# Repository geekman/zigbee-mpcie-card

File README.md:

CC2538 Zigbee mPCIe Adapter
============================

For use with [zigbee2mqtt](https://www.zigbee2mqtt.io/).

This card is basically a USB-to-serial adapter for the CC2538 + CC2592 PA Zigbee module.
It is intended for use in host devices that accept mPCIe cards, instead of having a Zigbee dongle sticking out of the USB port.
The antenna connection is also brought out to an external SMA connector via a U.FL pigtail.

As with most of my boards, this was designed to be flexible. The TX and RX pins from the module are clearly marked, so that the card can be repurposed as a generic serial device mPCIe card.
There are also various test points for I²C, as well as control for the WLAN/WWAN LEDs that are on the host machine.

This project is authored in [KiCad EDA](https://www.kicad.org/).
You can find schematics and the BOM under the [Releases](https://github.com/geekman/zigbee-mpcie-card/releases) section.

Assembly Instructions
======================

Please be aware that there are a few variations of this CC2538 module with different pinouts and dimensions.
The one I bought, and used in this mPCIe card, is available on [AliExpress here](https://www.aliexpress.com/item/4000748032872.html).
Also note that the presence of an on-board antenna; the module needs to be physically configured to use the U.FL connector instead of the on-board antenna.
You will need to indicate this to the seller, or you can modify it yourself by moving a capacitor (or resistor, not sure what that part is).

The card has support for native USB connectivity to the CC2538, but it is not used. 
As such, the component on the back side should not be populated, as well as R2 on the front side. The BOM file has these parts marked as DNP.

Additionally, Q2 was added for an ESP8266-style auto reset, but since the `cc2538-bsl` does not support this style of bootloader invocation, the pins of Q2 need to be manually bridged. The new revision of PCB has these connections marked out on the silkscreen.

Testing
--------

When inserted, the card should be detected as a CP2102N USB device on the host.

You need the [cc2538-bsl](https://github.com/JelmerT/cc2538-bsl) Python tool, 
which only depends on `pyserial`.
Note that the tool will try to reconnect to the port with an increased baud rate for faster transfer speeds, but this was causing problems for me. Use `-b` to set a fixed baud rate, and choose a lower value for stability.

You can test that the mPCIe card is properly detected by reading from the CC2538 with `-r`:

```
$ python3 cc2538-bsl.py -b 500000 -r test.bin
Opening port /dev/ttyUSB0, baud 500000
Connecting to target...
CC2538 PG2.0: 512KB Flash, 32KB SRAM, CCFG at 0x0027FFD4
Primary IEEE Address: 00:12:4B:00:19:4A:F1:CE
Reading 524288 bytes starting at address 0x200000
 0x200xxx: 0xffffffff
```

If you do specify the `-V` verbose flag, you see that chip ID for the CC2538 has been correctly detected:

```
$ python3 cc2538-bsl.py -V -r test.bin
Opening port /dev/ttyUSB0, baud 500000
Connecting to target...
*** sending synch sequence
Got 0 additional bytes before ACK/NACK
*** GetChipId command (0x28)
Got 0 additional bytes before ACK/NACK
*** received 6 bytes
*** GetStatus command (0x23)
Got 0 additional bytes before ACK/NACK
*** received 3 bytes
Command Successful
    Version 0x0000B964
    Target id 0xb964, CC2538
  .
  .
  .
```

Firmware Flashing
==================

You can download a zigbee2mqtt-compatible firmware here:

- <https://github.com/jethome-ru/zigbee-firmware/tree/master/ti/coordinator/cc2538_cc2592>

Here are some other firmware for reference:

- <https://github.com/egony/MODKAM-STICK-V3/tree/master/firmware/cc2538/Riverieline_2020-02>
- <https://github.com/Koenkk/Z-Stack-firmware/tree/master/coordinator>

You can choose either one; I went with the JetHome one.

Use the `cc2538-bsl.py` tool with `-w -v` to write and verify the firmware file.
Both the `.bin` and `.hex` contain the same firmware, just in a different format.

```
$ python3 cc2538-bsl.py -b 115200 -w -v JH_2538_2592_ZNP_UART_20201010.bin
Opening port /dev/ttyUSB0, baud 115200
Reading data from JH_2538_2592_ZNP_UART_20201010.bin
Cannot auto-detect firmware filetype: Assuming .bin
Connecting to target...
CC2538 PG2.0: 512KB Flash, 32KB SRAM, CCFG at 0x0027FFD4
Primary IEEE Address: 00:12:4B:00:19:4A:F1:CE
Writing 524256 bytes starting at address 0x00200000
Write 232 bytes at 0x0027FEF88
    Write done
Verifying by comparing CRC32 calculations.
    Verified (match: 0x6273805e)
```

You should now see the power LED on the mPCIe card light up.

Bootloader "Backdoor"
----------------------

Note that while the serial bootloader is a convenient way to program the CC2538, it may also be disabled by the firmware developer for security reasons.

The firmware images provided above all have this "bootloader backdoor" enabled, so that newer firmware can be flashed via the serial port.
This is done by setting some bits in the Customer Configuration Area (CCA) to enable the backdoor, and allowing for activation via pin `PA7`.
For more information, see the SWRA466 document here: <https://www.ti.com/lit/pdf/swra466>

You can verify this by opening the firmware HEX file and seeing the value `0xF7` set at `0x0027.FFD7`. (Actually the write begins at `0x27FFD4` to write a 32-bit value `FF FF FF F7`)

If you do not flash these bytes into the CCA, the serial bootloader can no longer be accessed and you will need JTAG to program the device. The connector has been brought out to the back side of the card, in case this is needed.

License
========
  
**cc2538-mpcie-card is licensed under the TAPR Open Hardware License (https://www.tapr.org/OHL).**

Copyright (C) 2021 Darell Tan

The TAPR Open Hardware License ("OHL") agreement provides a legal
framework for Open Hardware projects.
The OHL addresses unique issues involved in the creation of tangible,
physical things, but does not cover software, firmware, or code loaded
into programmable devices.

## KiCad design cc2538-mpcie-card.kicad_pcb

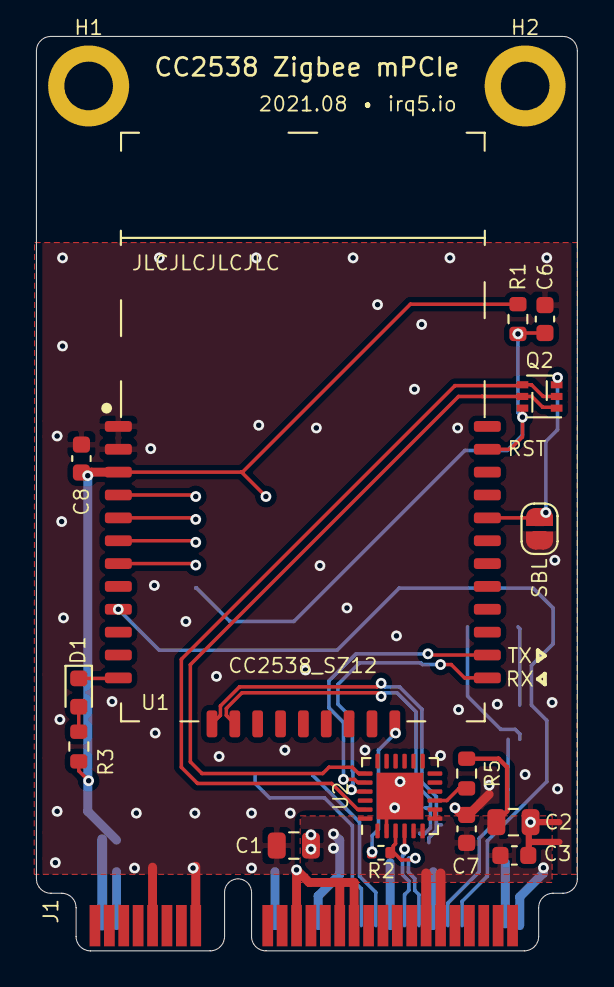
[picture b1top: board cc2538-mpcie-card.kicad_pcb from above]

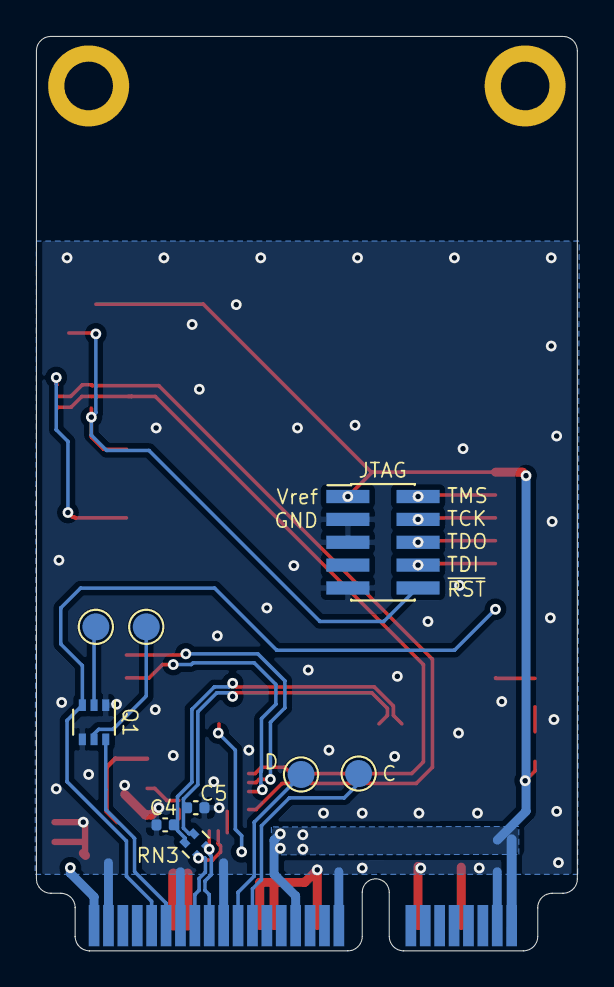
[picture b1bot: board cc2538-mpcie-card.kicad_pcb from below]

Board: 2 copper layers, 30.1 x 50.8 mm, 27 parts (9 on the bottom side), 26 nets.

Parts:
C1, C2: 47uF; C_0805_2012Metric
C3, C7: 0.1uF; C_0603_1608Metric
C4, C5: 47pF; C_0402_1005Metric
C6: 1nF; C_0603_1608Metric
C8: 10uF; C_0603_1608Metric
D1: LED_Small; LED_0603_1608Metric
H1, H2: MountingHole_Pad; MountingHole_2.7mm_M2.5_ISO7380_Pad
J1: Bus_PCI_Express_Mini; mPCIe_Card_Edge
J2: Conn_ARM_JTAG_SWD_10; PinHeader_2x05_P1.27mm_Vertical_SMD
JP1: SolderJumper_2_Open; SolderJumper-2_P1.3mm_Open_RoundedPad1.0x1.5mm
Q1, Q2: MUN5214DW1; SOT-363_SC-70-6
R1, R3, R5: 4K7; R_0603_1608Metric
R2: 1K5; R_0402_1005Metric
RN3: 33R; R_Array_Convex_2x0402
TP1: SDA; TestPoint_Pad_D1.5mm
TP2: SCL; TestPoint_Pad_D1.5mm
TP3: LED_WLAN; TestPoint_Pad_D1.5mm
TP4: LED_WWAN; TestPoint_Pad_D1.5mm
U1: CC2538_SZ12; CC2538_SZ12_Module
U2: CP2102N-A01-GQFN24; QFN-24-1EP_4x4mm_P0.5mm_EP2.6x2.6mm

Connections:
+3V3: C1.1, C2.1, C3.1, C7.2, C8.2, J1.2, J1.24, J1.39, J1.41, J1.52, J2.1, R1.2, R3.2, R5.1, U1.3, U2.5, U2.6, U2.7, U2.8
/CC_RST: C6.2, J2.10, Q2.6, R1.1, U1.32
/CC_RX: U1.22, U2.21
/CC_SBL: JP1.1, Q2.3, U1.29
/CC_TX: U1.23, U2.20
/CC_USB+: C4.1, RN3.4, U1.13
/CC_USB-: C5.2, RN3.3, U1.14
/USB+: J1.38, R2.2, RN3.1, U2.3
/USB-: J1.36, RN3.2, U2.4
/USB_FS_PU: R2.1, U1.21
/~LED_ACT: J1.44, Q1.3, U1.9
/~LED_PWR: D1.1, U1.12
/~LED_WWAN: J1.42, Q1.6
GND: C1.2, C2.2, C3.2, C4.2, C5.1, C6.1, C7.1, C8.1, J1.4, J1.9, J1.15, J1.18, J1.21, J1.26, J1.27, J1.29, J1.34, J1.35, J1.37, J1.40, J1.43, J1.50, J2.3, J2.5, J2.9, JP1.2, Q1.1, Q1.4, U1.1, U1.2, U2.2, U2.25
unnamed: D1.2, R3.1
unnamed: J1.30, TP2.1
unnamed: J1.32, TP1.1
unnamed: J2.2, U1.4
unnamed: J2.4, U1.5
unnamed: J2.6, U1.6
unnamed: J2.8, U1.7
unnamed: Q1.2, TP4.1
unnamed: Q1.5, TP3.1
unnamed: Q2.1, Q2.5, U2.19
unnamed: Q2.2, Q2.4, U2.23
unnamed: R5.2, U2.9

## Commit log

2021-04-16 Initial layout complete.
2021-04-16 Reworked USB, added power LED & cap
    The USB conection used to have dangling stubs, due to the likely
    unpopulated direct connection to the CC2538 native USB. It has now been
    reworked to use 0402 components, and the series resistor now rests
    directly on the vias, minimizing the amount of stub. Although it's just
    low speed USB, I doubt it would affect much.
    Additionally, wired up the activity LED (PB4) to the system's WLAN
2021-04-16 Added PCB markings & text
    - Labelled pinout for JTAG connector
    - Added PCB "title" & date
    - Added PCB manufacturer number marker
2021-04-16 Added PCB dimension markings
2021-04-17 Made card edge component "virtual"
    This prevents it from showing up in the BOM.
2021-04-17 Fix up component values
2021-04-24 Added document title & rev, and more GND vias
2021-04-25 Totally forgot to connect RXD/TXD serial lines
2021-04-25 Added RX/TX marking to module
2021-04-25 Marking for SCL should be C(lock)
2021-04-26 Updated Gerber generation settings
2021-07-29 Made curves 0.8mm radius, instead of 0.5mm
    After receiving the first batch of prototype boards, the curves don't
    look very prominent -- still a bit sharp on the corners. Not sure if
    that's attributed to the manufacturing process, but I thought I'd
    increase the curve radius to make it smoother.
2021-07-29 Increased GND plane clearance to 0.35mm
    The current GND plane is too near the edge in the prototype boards.
    Increased the clearance because it is unnecessary to have such a tight
    clearance for the GND plane anyway.
2021-08-08 Reduce thermal spokes to 0.3mm
    Found it difficult to solder the GND pins of the Zigbee module. I'm not
    sure if the heat was being conducted away by the GND plane on the
    castellated GND pads of the module, or by the GND plane on this board.
    In either case, it's safer to just reduce the spoke widths of the copper
    pours, since 0.508mm for thermal spokes is an overkill anyway. In
    addition, thermal clearance is also increased to pull the pours away
2021-08-08 Standardize resistors to 4K7
    The LED can also use 4K7 (whether red or green) since it should be
    bright enough.
    Additionally, clarify that C6 (RST cap) must be 1nF max in order not to
    interfere with software reset via the CP2012. It looks like the Python
    script doesn't have any delays when toggling the RTS pin, so we
    shouldn't use anything higher (like 100nF for C7).
2021-08-09 Added Q2 bridge silkscreen & some schematic text
2021-08-09 Added DNP field to schematic
    This marks out the components that we added for the "dev board"
    functionality, and native USB parts.
    1 - DNP
    2 - populate for native USB
2021-08-09 Updated PCB, bumped revision numbers
2021-08-09 Added README
